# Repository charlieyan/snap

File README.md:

### What is this project?
**snap** is a project to make a small simple microsd camera

### Roadmap:
- [X] &nbsp; OpenLog write data to it
- [ ] &nbsp; Read bits off of camera

### Notes

- Switched to Teensy 3.2 for faster onboard processor 75 MHz, 32-bit
- Teensy comes with 2 programs: HalfKay which switches the LED lights, and  whatever program you load through HalfKay bootloader

### Useful links:
- https://forum.processing.org/one/topic/serial-transfer-jpeg-from-arduino.html
- http://stackoverflow.com/questions/18748205/receiving-jpeg-photos-from-arduino-on-pc-in-binary-format
- http://stackoverflow.com/questions/18748205/receiving-jpeg-photos-from-arduino-on-pc-in-binary-format
- http://stackoverflow.com/questions/16724214/writing-images-with-an-arduino
- https://www.google.com/search?q=arduino+write+chars+to+jpeg&oq=arduino+write+chars+to+jpeg&aqs=chrome..69i57.3711j0j1&sourceid=chrome&ie=UTF-8
- https://github.com/Bodmer/JPEGDecoder
- https://github.com/MakotoKurauchi/JPEGDecoder
- https://www.google.com/search?q=pico+jpeg+library&oq=pico+jpeg+library&aqs=chrome..69i57.1999j0j1&sourceid=chrome&ie=UTF-8#q=picojpeg+github
- https://github.com/aron-bordin/PNG-Arduino-Framework
- https://github.com/elanthis/upng
- http://png-arduino-framework.readthedocs.io/
- https://hackaday.io/project/1313-openmv

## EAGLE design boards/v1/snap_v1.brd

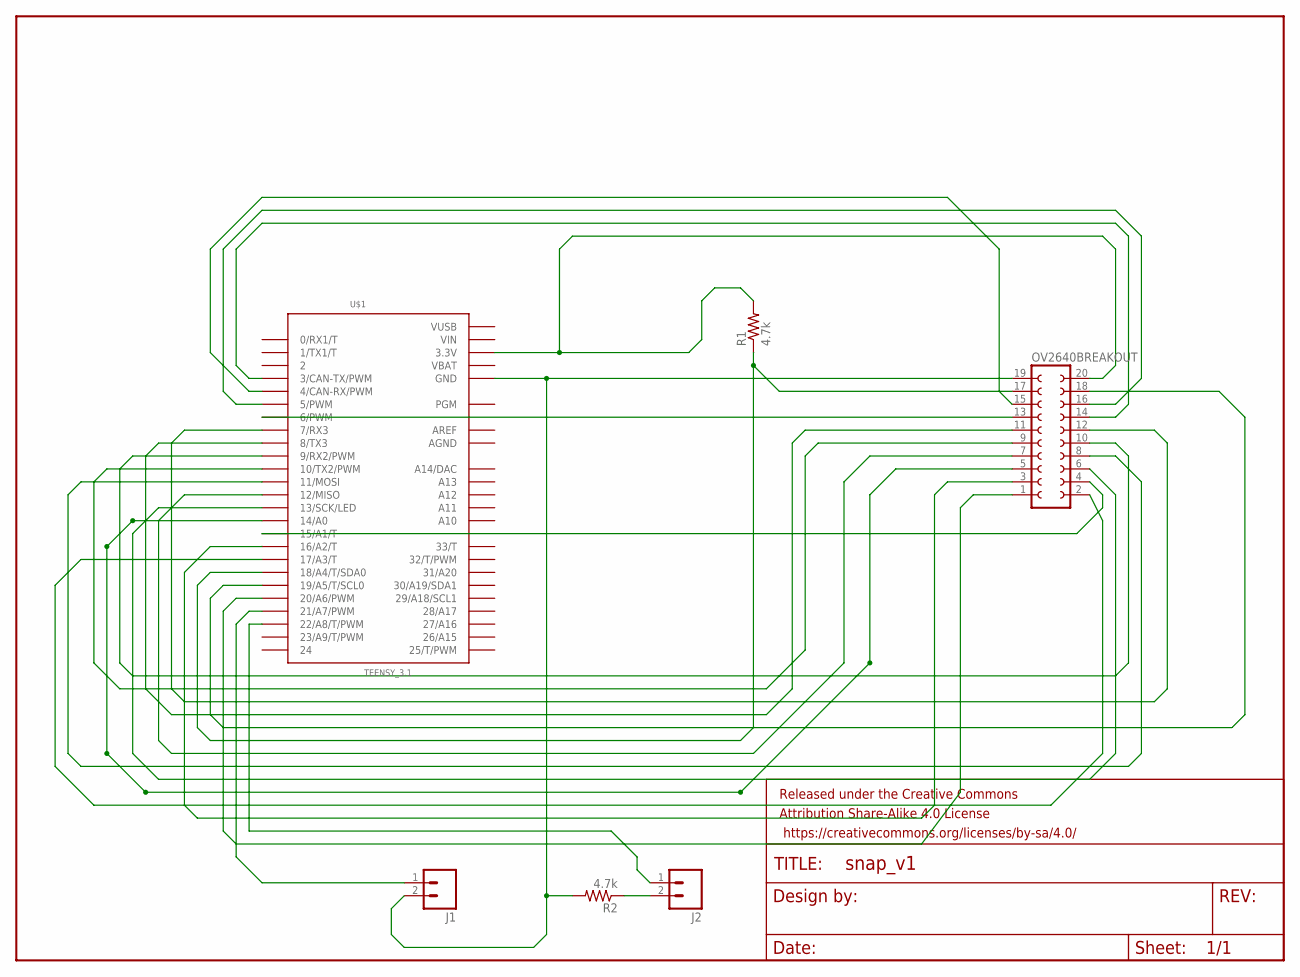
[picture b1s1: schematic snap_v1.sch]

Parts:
FRAME1: FRAME-LETTER; CREATIVE_COMMONS
J1, J2: M02PTH; 1X02
OV2640BREAKOUT: FE10-2
R1, R2: 4.7k; AXIAL-0.3EZ
U$1: TEENSY_3.1; TEENSY_3.0-3.2_ALL_PINS_&_PADS

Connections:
AGND: U$1.AGND
AREF: U$1.AREF
D0: OV2640BREAKOUT.6, U$1.13 (13/SCK/LED)
D1: OV2640BREAKOUT.5, U$1.14/A0
D2: OV2640BREAKOUT.8, U$1.11 (11/MOSI)
D3: OV2640BREAKOUT.7, U$1.12 (12/MISO)
D4: OV2640BREAKOUT.10, U$1.9 (9/RX2/PWM)
D5: OV2640BREAKOUT.9, U$1.10 (10/TX2/PWM)
D6: OV2640BREAKOUT.12, U$1.7 (7/RX3)
D7: OV2640BREAKOUT.11, U$1.8 (8/TX3)
HREF: OV2640BREAKOUT.16, U$1.5 (5/PWM)
unnamed: OV2640BREAKOUT.17, R1.P$1 (1), U$1.18/A4 (18/A4/T/SDA0)
unnamed: J2.2, R2.P$1 (1)
PCLK: OV2640BREAKOUT.13, U$1.6 (6/PWM)
PWDN: OV2640BREAKOUT.2, U$1.17/A3 (17/A3/T)
RST: OV2640BREAKOUT.1, U$1.20/A6 (20/A6/PWM)
SCLK: OV2640BREAKOUT.18, U$1.19/A5 (19/A5/T/SCL0)
STATUSLED: J1.1, U$1.21/A7 (21/A7/PWM)
STATUSLEDGND: J1.2, OV2640BREAKOUT.19, R2.P$2 (2), U$1.GND, U$1.GND1 (GND), U$1.GND2 (GND)
SWITCH: J2.1, U$1.22/A8 (22/A8/T/PWM)
VBAT: U$1.VBAT
VCCPULLUP: OV2640BREAKOUT.20, R1.P$2 (2), U$1.3.3V, U$1.3.3V1 (3.3V), U$1.3.3V2 (3.3V)
VIN: U$1.VIN
VSYNC: OV2640BREAKOUT.15, U$1.4 (4/CAN-RX/PWM)
VUSB: U$1.VUSB
XCLK: OV2640BREAKOUT.14, U$1.3 (3/CAN-TX/PWM)
Y0: OV2640BREAKOUT.4, U$1.15/A1 (15/A1/T)
Y1: OV2640BREAKOUT.3, U$1.16/A2 (16/A2/T)

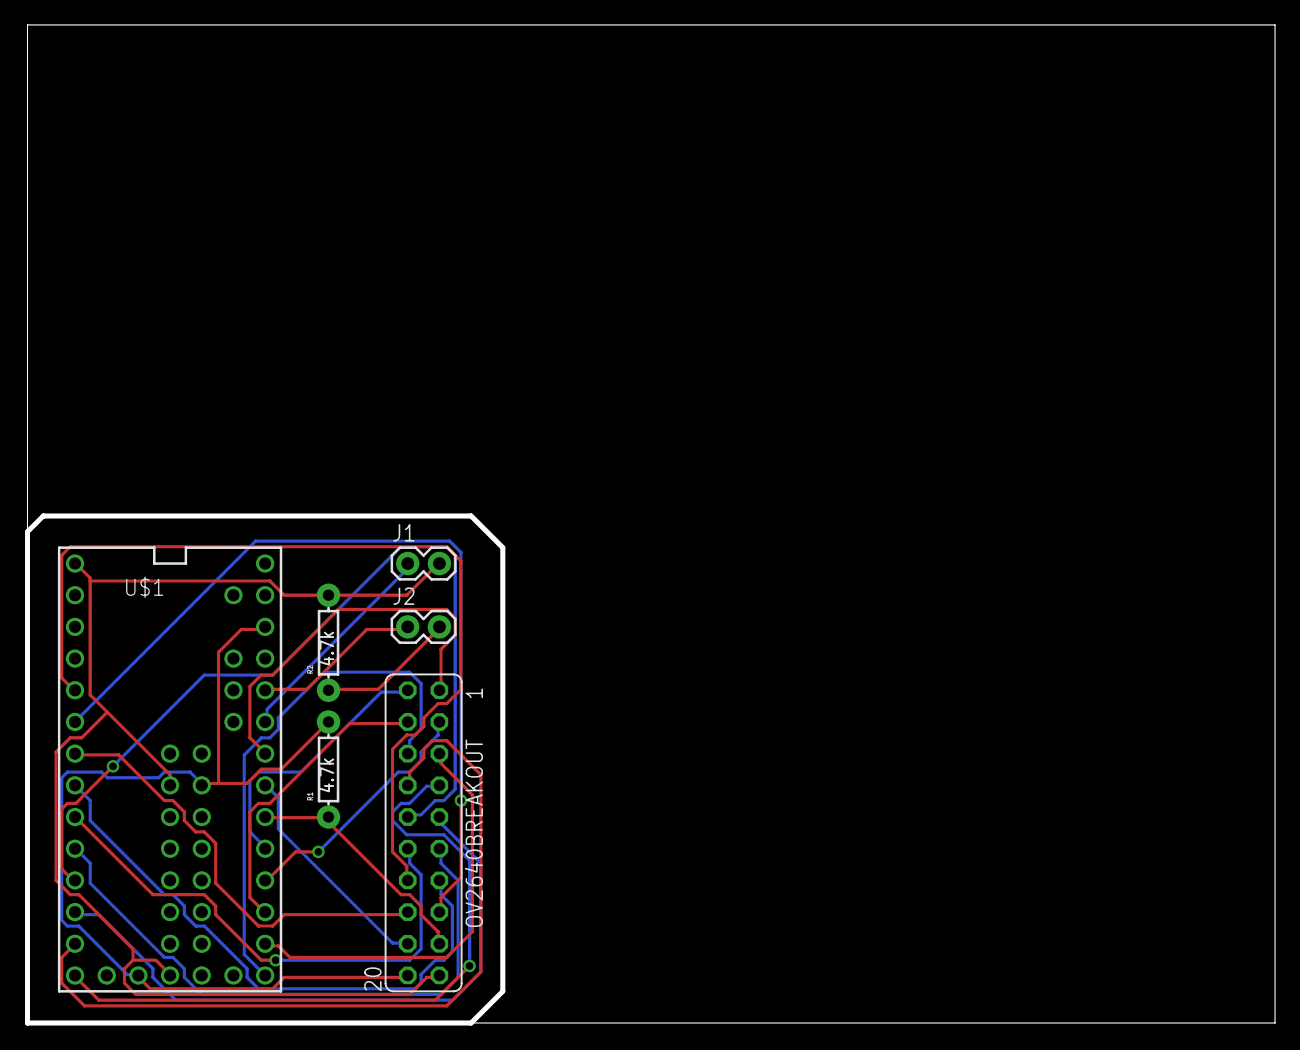
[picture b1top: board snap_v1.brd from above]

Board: 2 copper layers, 99.8 x 79.8 mm, 7 parts (0 on the bottom side), 23 nets.

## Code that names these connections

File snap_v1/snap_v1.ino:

#include <Wire.h>
#include <stdio.h>
#include <stdlib.h>     /* strtol */
#include "Sccb.h"
#include "ov2640_regs.h"

#define OV2640_SCCB_ADDRESS 0x30 /* 0011 110 0 = 60, but Wire takes care of last bit so 30 */

#define SCL_PIN 18
#define SDA_PIN 19

#define VSYNC 20
#define HREF  21
#define PCLK  17

#define D7    16
#define D6    23
#define D5    15
#define D4    4
#define D3    14
#define D2    5
#define D1    13
#define D0    6

#define Y1    12
#define Y0    7

#define PWDN  -1 // not connected
#define RST   11
#define XCLK  22 // 8 MHz output

#define TX    1 // RX1 on openlog 
#define RX    0 // TX0 on openlog

#define SWI   2
#define LED   3

String readString;
Sccb sccb = Sccb();
bool pulseLED = false;
bool ledOn = false;

// OV7670 register values
const struct regval_list ov2640_regs[] = {
  {BANK_SEL,    BANK_SEL_SENS},
  {COM7,        COM7_SRST}, // system reset
  {0xFF, 0xFF}  // End marker
};

void setup_pins() {
  pinMode(VSYNC,  INPUT);
  attachInterrupt(digitalPinToInterrupt(VSYNC), vsync_rising_cb, RISING);
  attachInterrupt(digitalPinToInterrupt(VSYNC), vsync_falling_cb, FALLING);
  pinMode(HREF,   INPUT);
  pinMode(PCLK,   INPUT);
  pinMode(D7,     INPUT);
  pinMode(D6,     INPUT);
  pinMode(D5,     INPUT);
  pinMode(D4,     INPUT);
  pinMode(D3,     INPUT);
  pinMode(D2,     INPUT);
  pinMode(D1,     INPUT);
  pinMode(D0,     INPUT);
  pinMode(Y1,     INPUT);
  pinMode(Y0,     INPUT);

  pinMode(RST,    OUTPUT);
  pinMode(XCLK,   OUTPUT);

  pinMode(LED,    OUTPUT);
  pinMode(SWI,    INPUT);

  pinMode(TX,     OUTPUT);
  pinMode(RX,     INPUT);  
}

void vsync_rising_cb() {
  Serial.println("vsync rising");
}

void vsync_falling_cb() {
  Serial.println("vsync falling");
}

void setup() {
  Wire.begin();
  setup_pins();
  
  delay(100);
  analogWriteFrequency(XCLK, 8000000); // Create 8 MHz clock output for XCLK, which drives the PLL that goes downstreams to timing etc.
  analogWrite(XCLK, 127);; // 50% duty cycle
  delay(100);

  int found_address = sccb.scanForDevices();
  if (found_address == OV2640_SCCB_ADDRESS) {
    sccb._device_id = found_address;
  }

  Serial.begin(115200);  // start serial for debug output
  delay(1000);
}
void loop() {
  while (Serial.available()) {
    char c = Serial.read(); // gets one byte from serial buffer
    readString += c; //makes the string readString
    delay(2); //slow looping to allow buffer to fill with next character
  }
  if (readString.length() > 0) {
    Serial.println(readString);
  }

  if (readString == "status") {
    Serial.println(sccb._device_id);
  }
  else if (readString == "led") {
    pulseLED = !pulseLED;
  }
  else if (readString[0] == 'r') {
    String rest = readString.substring(1);

    long int x;
    char* pEnd;
    x = strtol(rest.c_str(),&pEnd,16);
    Serial.println(x);

    byte bank_select = sccb.readRegister(OV2640_SCCB_ADDRESS, x);
    Serial.println(bank_select);
  }
  else if (readString[0] == 'w') {
    if (readString.length() == 10) {
      String sub_address = readString.substring(1, 5);
      long int sub_address_int;
      char* sub_address_c;
      sub_address_int = strtol(sub_address.c_str(),&sub_address_c,16);

      String data = readString.substring(6, 10);
      long int data_int;
      char* data_c;
      data_int = strtol(data.c_str(),&data_c,16);

      int result = sccb.writeRegister(OV2640_SCCB_ADDRESS, (byte)sub_address_int, (byte)data_int);
      Serial.print("writing to ");
      Serial.print(sub_address_int);
      Serial.print(" finished with ");
      Serial.println(result);
    }
  }

  readString = "";

  if (pulseLED) {
    if (!ledOn) {
      digitalWrite(LED, HIGH);
    }
    else {
      digitalWrite(LED, LOW); 
    }
    ledOn = !ledOn;
  }
}

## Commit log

2016-05-01 readme
2016-05-01 sccb datasheet
2016-08-03 snap work: setup for arduino script
2016-09-20 starting integration with camera
2016-11-05 ov2640 registers
2016-11-05 finished registers, start of sccb implementation
2016-11-15 more work on snap
2016-11-23 update snap_v1
2016-11-23 latest changes to firmware
2017-05-13 teensy_sd working
2017-05-13 recovering some i2c work from earlier
2017-05-15 changes to i2c to persist a test
2017-05-19 t3, still reading all 0's
2017-10-09 bringup: sccb bit banging working
2017-10-09 bringup: bitbang_attempt_4
2017-10-12 8 bit addresses sccb test, latest work
2018-04-14 more progress on ali42
2018-04-15 ali42 bringup
2018-04-16 got yuvs out of camera fifo
2018-04-16 starting on ali42 bringup with microsd
2018-05-13 ali42, more work, reading directly off serial
2019-06-21 platformio building

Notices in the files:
parts and their libraries:
SparkFun-Aesthetics: Licensing: Creative Commons ShareAlike 4.0 International - https://creativecommons.org/licenses/by-sa/4.0
SparkFun-Aesthetics: Released under the Creative Commons Attribution Share-Alike 4.0 License
SparkFun-Aesthetics: https://creativecommons.org/licenses/by-sa/4.0
